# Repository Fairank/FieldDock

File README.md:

# FieldDock · Fairank / 年糕

面向 iPhone 17 Pro Max 的模块化无线与硬件实验工具。主板将 Sub-GHz、NFC、125 kHz RFID、红外、iButton、GPIO 和存储接口集中在 **94 × 40 mm** 的板上；手机承担未来的界面和结果处理。

**K 版全板布线与数字制造文件检查已完成。当前发布的是未制作、未上电的工程样板设计，尚未完成整机装配采购放行，也没有 Apple 认证或 Flipper 功能等效实测。**

## 本次交付

| 内容 | 文件 | 当前状态 |
|---|---|---|
| 可编辑电路与 PCB | [KiCad 工程](cad/FD-MAIN-01.kicad_pro)、[主板](cad/FD-MAIN-01.kicad_pcb)、[22 页原理图 PDF](schematic/FieldDock-schematic-K.pdf) | 全板布线；KiCad 10.0.6 ERC/DRC 通过 |
| 制造资料 | [Gerber / 钻孔 ZIP](manufacturing/FieldDock-PCB-K-fabrication.zip)、[加工要求](manufacturing/PROCESS-K.md)、[文件说明](manufacturing/README.md) | 已导出并独立核对几何；供应商 CAM 接单确认待完成 |
| 元件与贴装 | [BOM 复核表](manufacturing/BOM-review.csv)、[395 件贴装坐标](manufacturing/FD-MAIN-01-populated-pos.csv) | 位置已核对；部分采购料号、替代料和底面角度约定待厂家确认 |
| 结构设计 | [STEP / STL 模型包](mechanical/FieldDock-mechanical-K.zip)、[参数与生成脚本](mechanical/) | 16 个零件及组件包络；安装孔对应一致，未做实物公差验证 |
| 基础驱动 | [C 驱动与主机测试](firmware/) | CC1101 识别读取、电源预算策略、GPIO 映射；没有完整可烧录固件 |
| 可审阅证据 | [发布状态](release-status.json)、[检查记录](checks/)、[验证说明](VALIDATION.md) | 对应本次文件哈希 |

## 检查结果

- PCB DRC：**0 未连接、0 错误、0 警告**；原理图 ERC：**0 违规**。启用范围与五项默认忽略规则保留在原始报告中，不表示所有可选规则都已执行。
- 原理图、最终 PCB 和布线模型：**1,260 个已分配引脚连接一致**；57 个明确标记的未使用引脚单独核对。
- 独立 Gerber/Excellon 解析：核对 **11,385 段走线、899 个贯穿过孔、907 个金属化钻孔/槽、10 个非金属化孔**，八层铜、外形和装配坐标一致。
- 机械包络检查：50 对检查对象，无非预期交叠；4 处自攻螺钉与底孔材料交叠为设计预期。它不包含尺寸公差、插拔力和线束弯曲验证。
- 基础驱动通过主机测试与 Cortex-M4 freestanding 对象编译；尚未链接整机镜像或上板测试。

```sh
python tools/verify_artifacts.py
python tools/verify_artifacts.py --release
```

第二条命令核验本版**裸 PCB 工程样板文件**的数字检查条件，不代表供应商已接单、整机可量产或硬件功能已通过。脚本不会自动运行 KiCad。

## 硬件范围

主控为 STM32WB5MMG，射频采用 CC1101 与 ST25R3916，并设 LF RFID、红外、iButton、隔离 GPIO、microSD 及反馈控制电路。Sub-GHz、NFC 和 LF 的完整协议、读写能力与距离需要固件和样板分别验证。

两个 USB-C 分别用于手机数据/低功率输入与 AUX 固定 5 V 辅助输入，包含电源选择、限流和反向电流保护设计。**本版不含电池；两个端口的电流预算不能相加。** USB 为全速 12 Mbit/s，iPhone App 的有线数据通道尚未完成。没有增加所谓“iPhone 芯片”。

CSI、雷达、UWB、宽带 SDR、热成像和镜头检查作为外部探头方向保留；本次主板发布不等于这些探头及其算法已全部实现。Flipper 官方功能是参考目标，并未复制其固件或宣称兼容替代。仓库不包含无线网络干扰功能。

八层、1.6 mm、沉金、所有贯穿过孔树脂填孔盖帽；使用 0.30/0.15 mm 和 0.35/0.20 mm 过孔。**0.15 mm 机械钻孔是非常规加价工艺**，须按 [加工规格](manufacturing/PROCESS-K.md) 单独确认，不能按普通双层板下单。主板下单前须让厂家确认最终 CAM、叠层、填孔和阻抗条件。

## 外壳与安装

外壳目标 100 × 46 × 18 mm，安装背板另占约 1.6 mm。提供参数化源码、装配 STEP 以及各零件 STEP/STL；内部电子元件使用保守包络，并非全部来自原厂的精确三维模型。接口插拔、手机摄像头避让、固定强度、天线线圈与装壳后的射频表现仍需试装。

## 预算与后续验证

[工程预算](manufacturing/BUDGET-K.md)：单套核心样机约 **¥1,534–3,820**；两套合计约 **¥2,049–4,941**。这些是估算，**均未包含尚未报价的 0.15 mm 钻孔附加费**，也不含手机、外部探头、射频调试和返版，不是最终价格上限。没有下单或取得厂家正式报价。

下一步是供应商 CAM 与料号确认、限流上电、电源切换/倒灌测试、射频与线圈调谐、手机通信以及外壳试装。详见 [验证顺序](VALIDATION.md)。原生图纸保留设计过程的标题栏版本；本次发布以 `release-status.json` 和文件校验清单确定对应关系。

## 署名和使用

Copyright © 2026 fairank，限其依法可保护并有权许可的原创贡献。年糕图标为本项目品牌。

原创贡献以 [FieldDock 非商业许可](LICENSE) 提供源码，个人可委托收费代工制作自用样机；对许可材料的商业使用需另行获得书面许可。这是 **noncommercial source-available** 项目，不使用 OSI 开源标识。KiCad 库及其衍生部分保留上游许可，见 [第三方说明](THIRD_PARTY_NOTICES.md) 和 [逐文件来源清单](licensing/library-inventory.csv)。不主张对通用电路方法、技术事实或独立实现的排他权。

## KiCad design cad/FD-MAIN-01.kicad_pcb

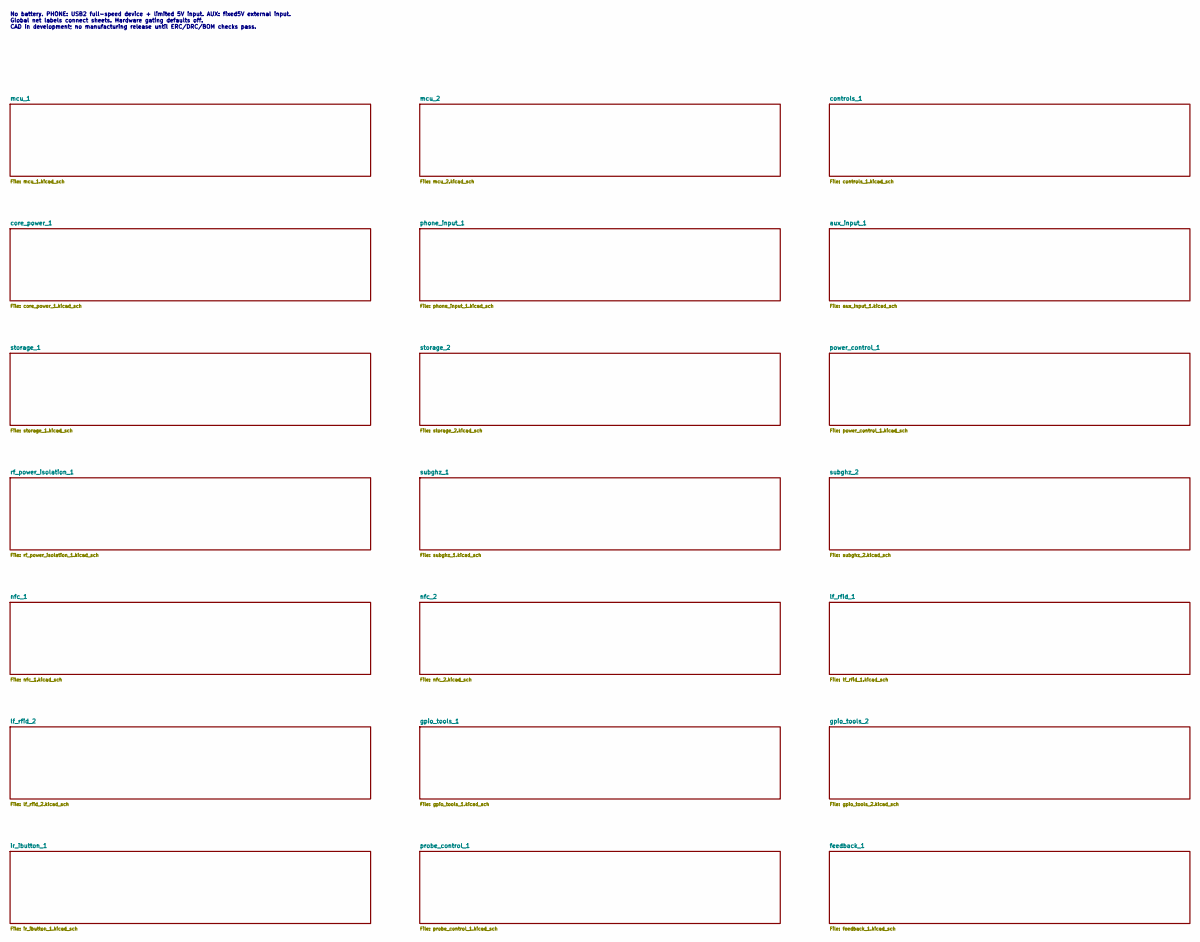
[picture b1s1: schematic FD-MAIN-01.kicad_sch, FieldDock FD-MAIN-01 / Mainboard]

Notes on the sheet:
No battery. PHONE: USB2 full-speed device + limited 5V input. AUX: fixed5V external input. Global net labels connect sheets. Hardware gating defaults off. CAD in development; no manufacturing release until ERC/DRC/BOM checks pass.

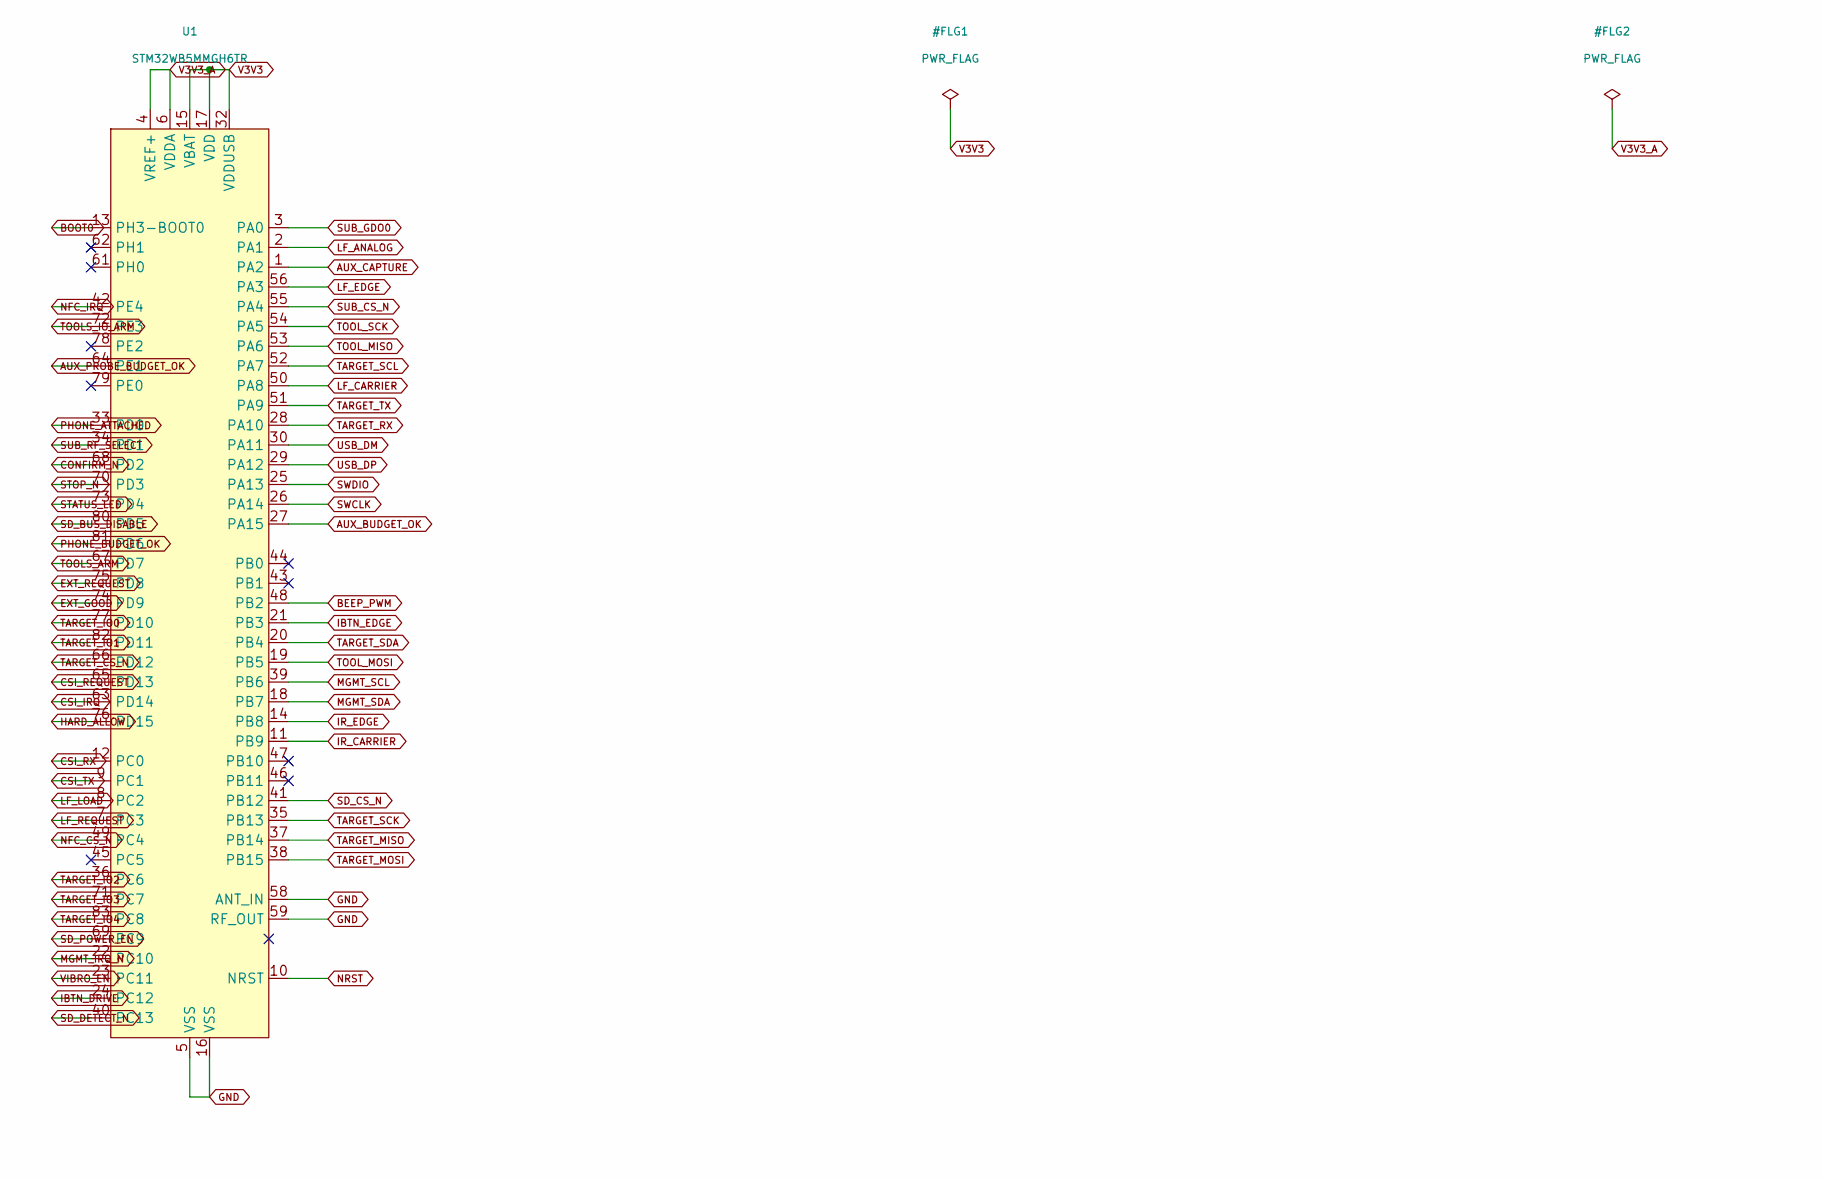
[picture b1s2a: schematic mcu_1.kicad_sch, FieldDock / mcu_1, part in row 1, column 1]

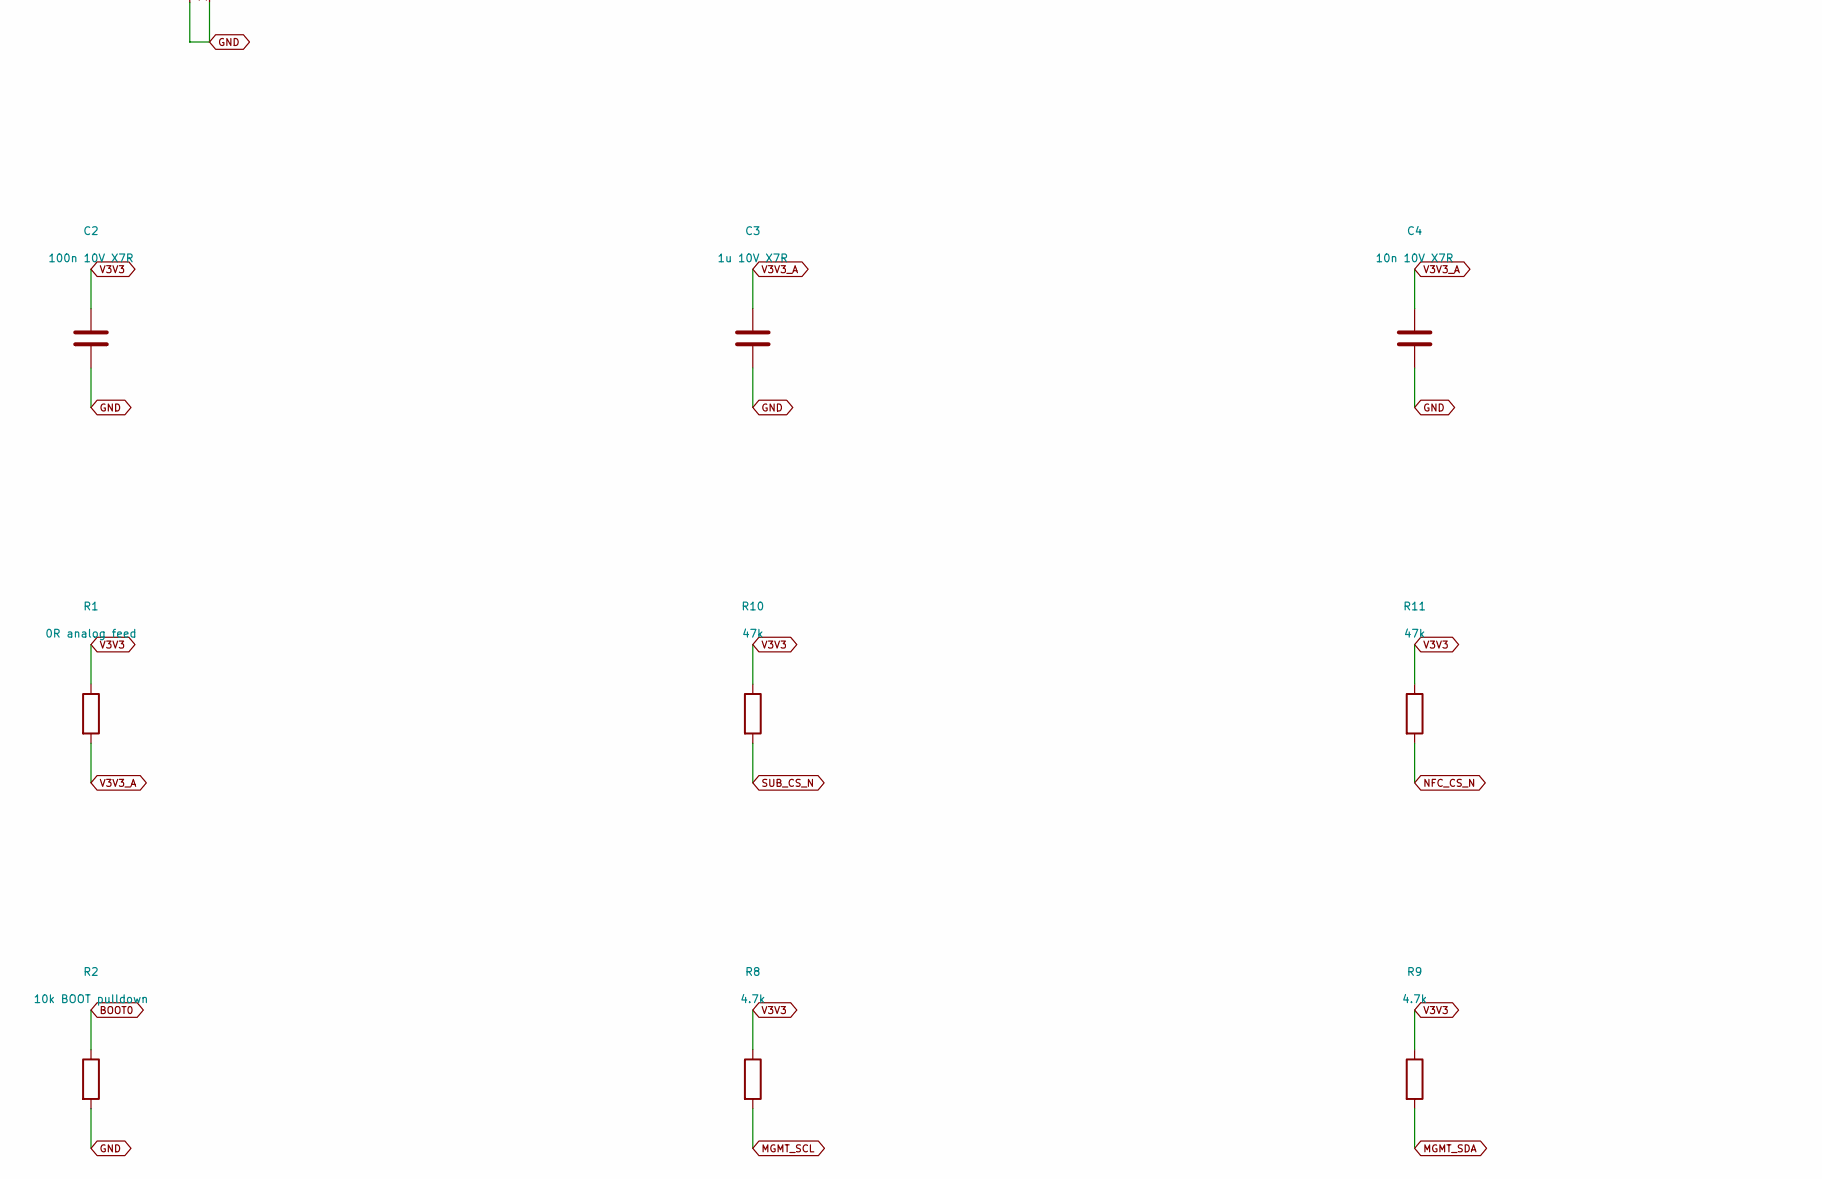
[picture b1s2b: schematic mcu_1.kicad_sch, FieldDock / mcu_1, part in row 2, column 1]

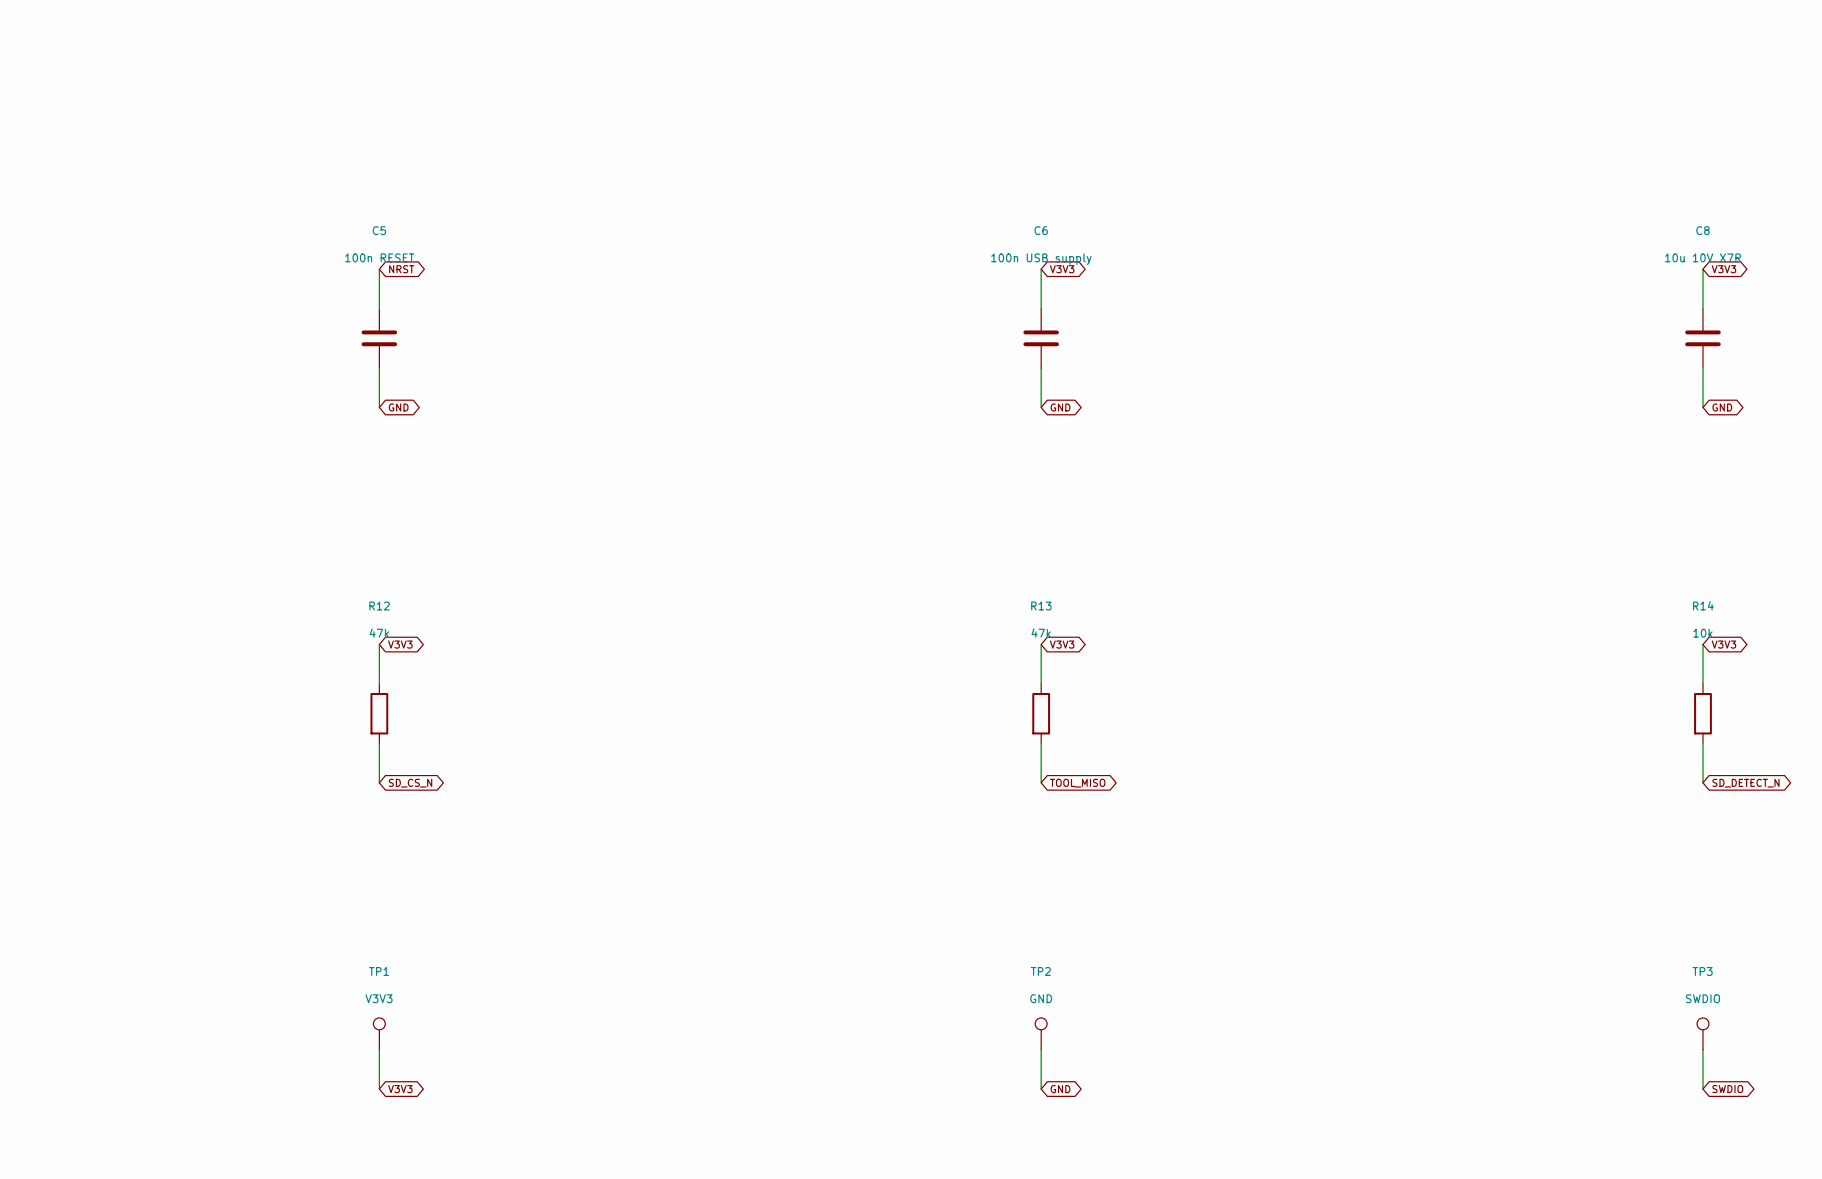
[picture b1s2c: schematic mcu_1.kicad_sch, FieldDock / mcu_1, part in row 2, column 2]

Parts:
C1: 4.7u 10V X7R; C_0805_2012Metric
C2: 100n 10V X7R; C_0603_1608Metric
C3: 1u 10V X7R; C_0603_1608Metric
C4: 10n 10V X7R; C_0603_1608Metric
C5: 100n RESET; C_0603_1608Metric
C6: 100n USB supply; C_0603_1608Metric
C8: 10u 10V X7R; C_0805_2012Metric
R1: 0R analog feed; R_0603_1608Metric
R2: 10k BOOT pulldown; R_0603_1608Metric
R8, R9: 4.7k; R_0603_1608Metric
R10, R11, R12, R13: 47k; R_0603_1608Metric
R14: 10k; R_0603_1608Metric
TP1: V3V3; TestPoint_Pad_D1.0mm
TP2: GND; TestPoint_Pad_D1.0mm
TP3: SWDIO; TestPoint_Pad_D1.0mm
U1: STM32WB5MMGH6TR; ST-SiP-LGA-86-11x7.3mm

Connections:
AUX_BUDGET_OK: U1.27 (PA15); also elsewhere on the board
AUX_CAPTURE: U1.1 (PA2); also elsewhere on the board
AUX_PROBE_BUDGET_OK: U1.64 (PE1); also elsewhere on the board
BEEP_PWM: U1.48 (PB2); also elsewhere on the board
BOOT0: R2.1, U1.13 (PH3-BOOT0); also elsewhere on the board
CONFIRM_N: U1.68 (PD2); also elsewhere on the board
CSI_IRQ: U1.63 (PD14); also elsewhere on the board
CSI_REQUEST: U1.65 (PD13); also elsewhere on the board
CSI_RX: U1.12 (PC0); also elsewhere on the board
CSI_TX: U1.9 (PC1); also elsewhere on the board
EXT_GOOD: U1.74 (PD9); also elsewhere on the board
EXT_REQUEST: U1.75 (PD8); also elsewhere on the board
GND: C1.2, C2.2, C3.2, C4.2, C5.2, C6.2, C8.2, R2.2, TP2.1, U1.5 (VSS), U1.16 (VSS), U1.31 (VSS), U1.57 (VSS), U1.58 (ANT_IN), U1.59 (RF_OUT), U1.60 (VSS), U1.84 (VSS), U1.86 (VSS); also elsewhere on the board
HARD_ALLOW: U1.76 (PD15); also elsewhere on the board
IBTN_DRIVE: U1.24 (PC12); also elsewhere on the board
IBTN_EDGE: U1.21 (PB3); also elsewhere on the board
IR_CARRIER: U1.11 (PB9); also elsewhere on the board
IR_EDGE: U1.14 (PB8); also elsewhere on the board
LF_ANALOG: U1.2 (PA1); also elsewhere on the board
LF_CARRIER: U1.50 (PA8); also elsewhere on the board
LF_EDGE: U1.56 (PA3); also elsewhere on the board
LF_LOAD: U1.8 (PC2); also elsewhere on the board
LF_REQUEST: U1.7 (PC3); also elsewhere on the board
MGMT_IRQ_N: U1.22 (PC10); also elsewhere on the board
MGMT_SCL: R8.2, U1.39 (PB6); also elsewhere on the board
MGMT_SDA: R9.2, U1.18 (PB7); also elsewhere on the board
NFC_CS_N: R11.2, U1.49 (PC4); also elsewhere on the board
NFC_IRQ: U1.42 (PE4); also elsewhere on the board
NRST: C5.1, U1.10 (NRST); also elsewhere on the board
PHONE_ATTACHED: U1.33 (PD0); also elsewhere on the board
PHONE_BUDGET_OK: U1.81 (PD6); also elsewhere on the board
SD_BUS_DISABLE: U1.80 (PD5); also elsewhere on the board
SD_CS_N: R12.2, U1.41 (PB12); also elsewhere on the board
SD_DETECT_N: R14.2, U1.40 (PC13); also elsewhere on the board
SD_POWER_EN: U1.69 (PC9); also elsewhere on the board
STATUS_LED: U1.73 (PD4); also elsewhere on the board
STOP_N: U1.70 (PD3); also elsewhere on the board
SUB_CS_N: R10.2, U1.55 (PA4); also elsewhere on the board
SUB_GDO0: U1.3 (PA0); also elsewhere on the board
SUB_RF_SELECT: U1.34 (PD1); also elsewhere on the board
SWCLK: U1.26 (PA14); also elsewhere on the board
SWDIO: TP3.1, U1.25 (PA13)
TARGET_CS_N: U1.66 (PD12); also elsewhere on the board
TARGET_IO0: U1.77 (PD10); also elsewhere on the board
TARGET_IO1: U1.82 (PD11); also elsewhere on the board
TARGET_IO2: U1.36 (PC6); also elsewhere on the board
TARGET_IO3: U1.71 (PC7); also elsewhere on the board
TARGET_IO4: U1.83 (PC8); also elsewhere on the board
TARGET_MISO: U1.37 (PB14); also elsewhere on the board
TARGET_MOSI: U1.38 (PB15); also elsewhere on the board
TARGET_RX: U1.28 (PA10); also elsewhere on the board
TARGET_SCK: U1.35 (PB13); also elsewhere on the board
TARGET_SCL: U1.52 (PA7); also elsewhere on the board
TARGET_SDA: U1.20 (PB4); also elsewhere on the board
TARGET_TX: U1.51 (PA9); also elsewhere on the board
TOOLS_ARM: U1.67 (PD7); also elsewhere on the board
TOOLS_IO_ARM: U1.72 (PE3); also elsewhere on the board
TOOL_MISO: R13.2, U1.53 (PA6); also elsewhere on the board
TOOL_MOSI: U1.19 (PB5); also elsewhere on the board
TOOL_SCK: U1.54 (PA5); also elsewhere on the board
USB_DM: U1.30 (PA11); also elsewhere on the board
USB_DP: U1.29 (PA12); also elsewhere on the board
V3V3: C1.1, C2.1, C6.1, C8.1, R1.1, R8.1, R9.1, R10.1, R11.1, R12.1, R13.1, R14.1, TP1.1, U1.15 (VBAT), U1.17 (VDD), U1.32 (VDDUSB); also elsewhere on the board
V3V3_A: C3.1, C4.1, R1.2, U1.4 (VREF+), U1.6 (VDDA)
VIBRO_EN: U1.23 (PC11); also elsewhere on the board

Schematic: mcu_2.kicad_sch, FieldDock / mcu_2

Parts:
TP4: SWCLK; TestPoint_Pad_D1.0mm
TP5: NRST; TestPoint_Pad_D1.0mm
TP6: CORE5; TestPoint_Pad_D1.0mm
TP7: EXT5; TestPoint_Pad_D1.0mm
TP8: PHONE5; TestPoint_Pad_D1.0mm

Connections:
CORE5: TP6.1; also elsewhere on the board
EXT5: TP7.1; also elsewhere on the board
NRST: TP5.1; also elsewhere on the board
PHONE5: TP8.1; also elsewhere on the board
SWCLK: TP4.1; also elsewhere on the board

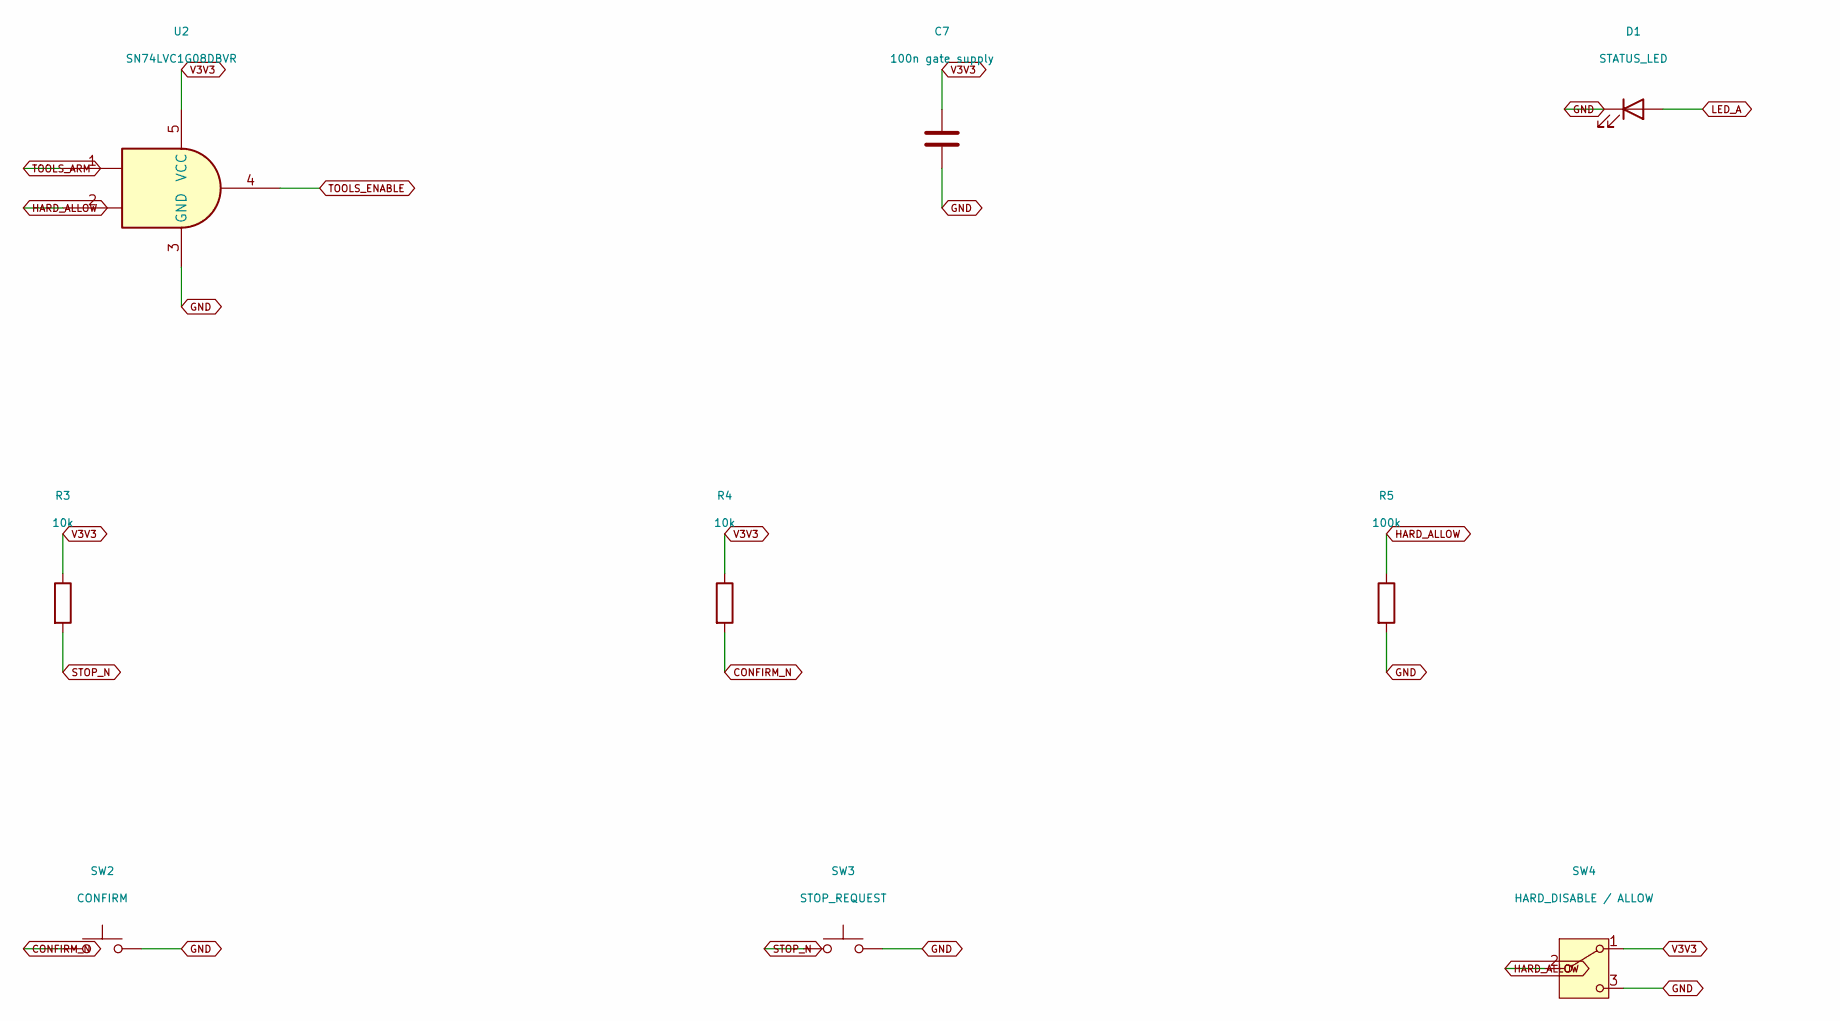
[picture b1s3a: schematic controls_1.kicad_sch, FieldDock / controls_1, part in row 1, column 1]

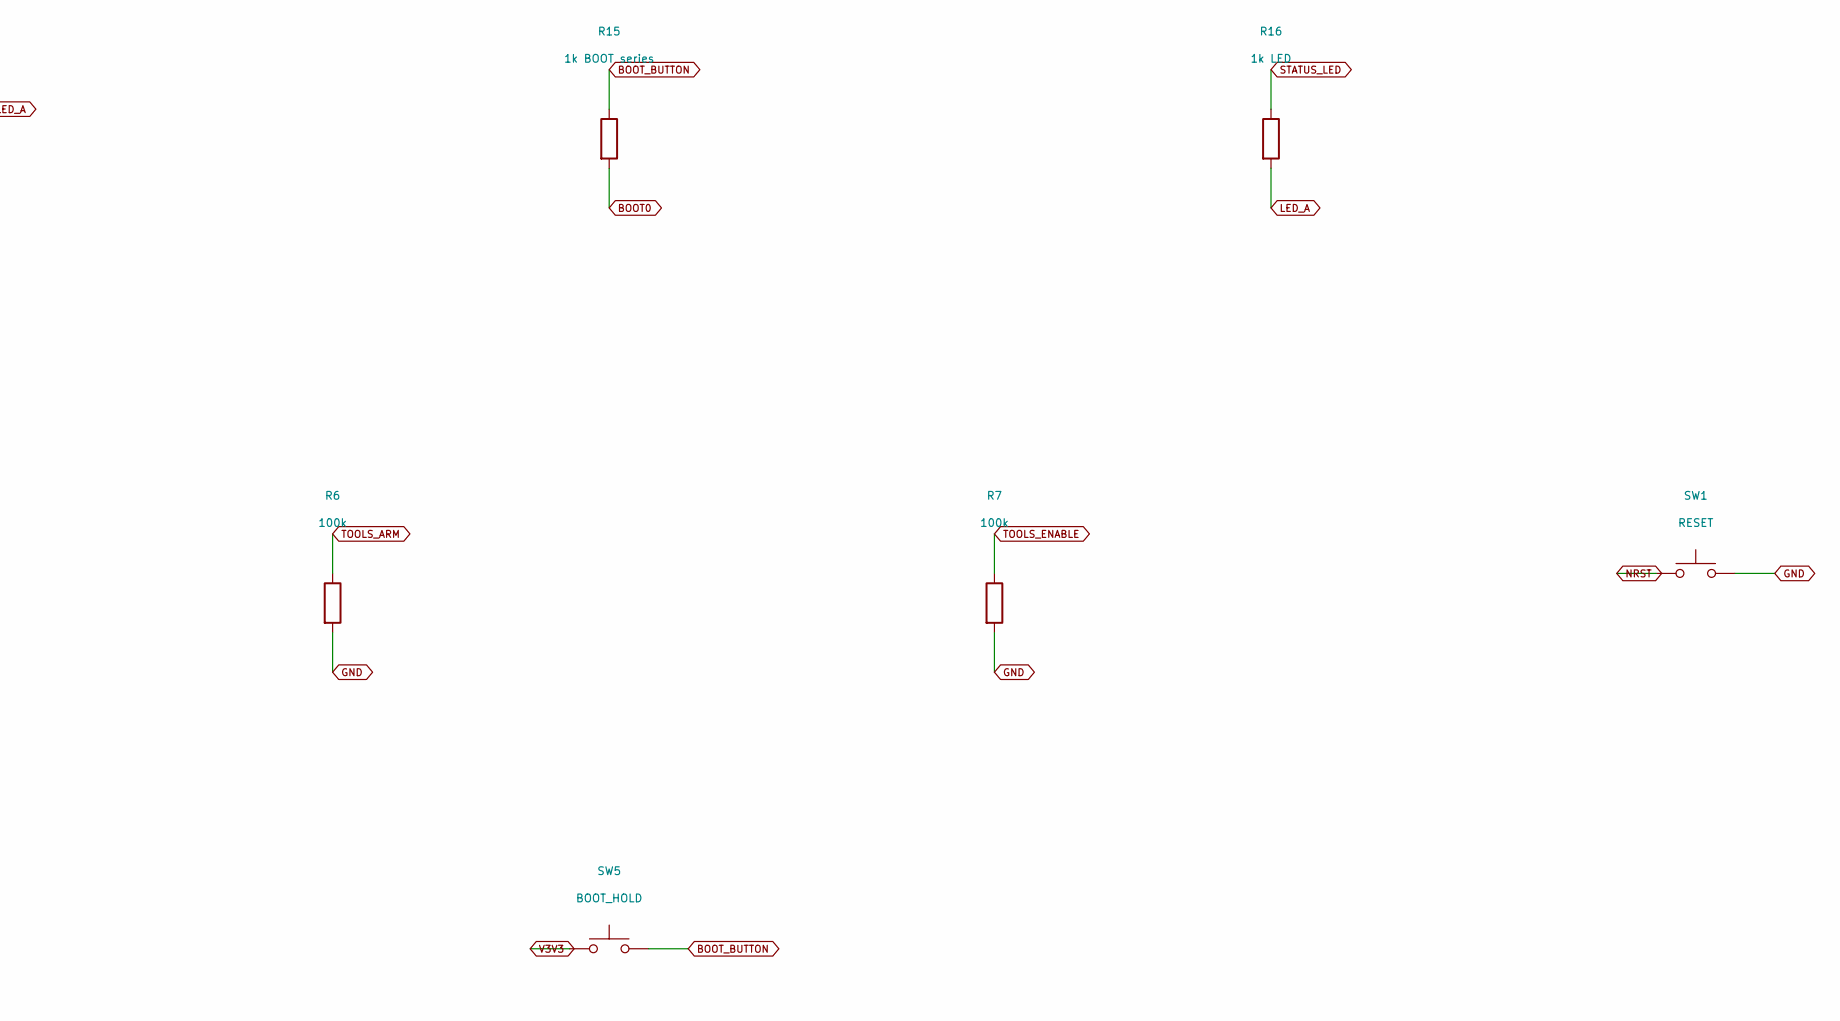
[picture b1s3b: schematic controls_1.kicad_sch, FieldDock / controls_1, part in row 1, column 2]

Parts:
C7: 100n gate supply; C_0603_1608Metric
D1: STATUS_LED; LED_0603_1608Metric
R3, R4: 10k; R_0603_1608Metric
R5, R6, R7: 100k; R_0603_1608Metric
R15: 1k BOOT series; R_0603_1608Metric
R16: 1k LED; R_0603_1608Metric
SW1: RESET; SW_SPST_TL3342
SW2: CONFIRM; SW_SPST_TL3342
SW3: STOP_REQUEST; SW_SPST_TL3342
SW4: HARD_DISABLE / ALLOW; SW_SPDT_CK_JS102011SAQN
SW5: BOOT_HOLD; SW_SPST_TL3342
U2: SN74LVC1G08DBVR; SOT-23-5

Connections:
BOOT0: R15.2; also elsewhere on the board
BOOT_BUTTON: R15.1, SW5.2
CONFIRM_N: R4.2, SW2.1; also elsewhere on the board
GND: C7.2, D1.1 (K), R5.2, R6.2, R7.2, SW1.2, SW2.2, SW3.2, SW4.3 (C), U2.3 (GND); also elsewhere on the board
HARD_ALLOW: R5.1, SW4.2 (B), U2.2; also elsewhere on the board
LED_A: D1.2 (A), R16.2
NRST: SW1.1; also elsewhere on the board
STATUS_LED: R16.1; also elsewhere on the board
STOP_N: R3.2, SW3.1; also elsewhere on the board
TOOLS_ARM: R6.1, U2.1; also elsewhere on the board
TOOLS_ENABLE: R7.1, U2.4; also elsewhere on the board
V3V3: C7.1, R3.1, R4.1, SW4.1 (A), SW5.1, U2.5 (VCC); also elsewhere on the board

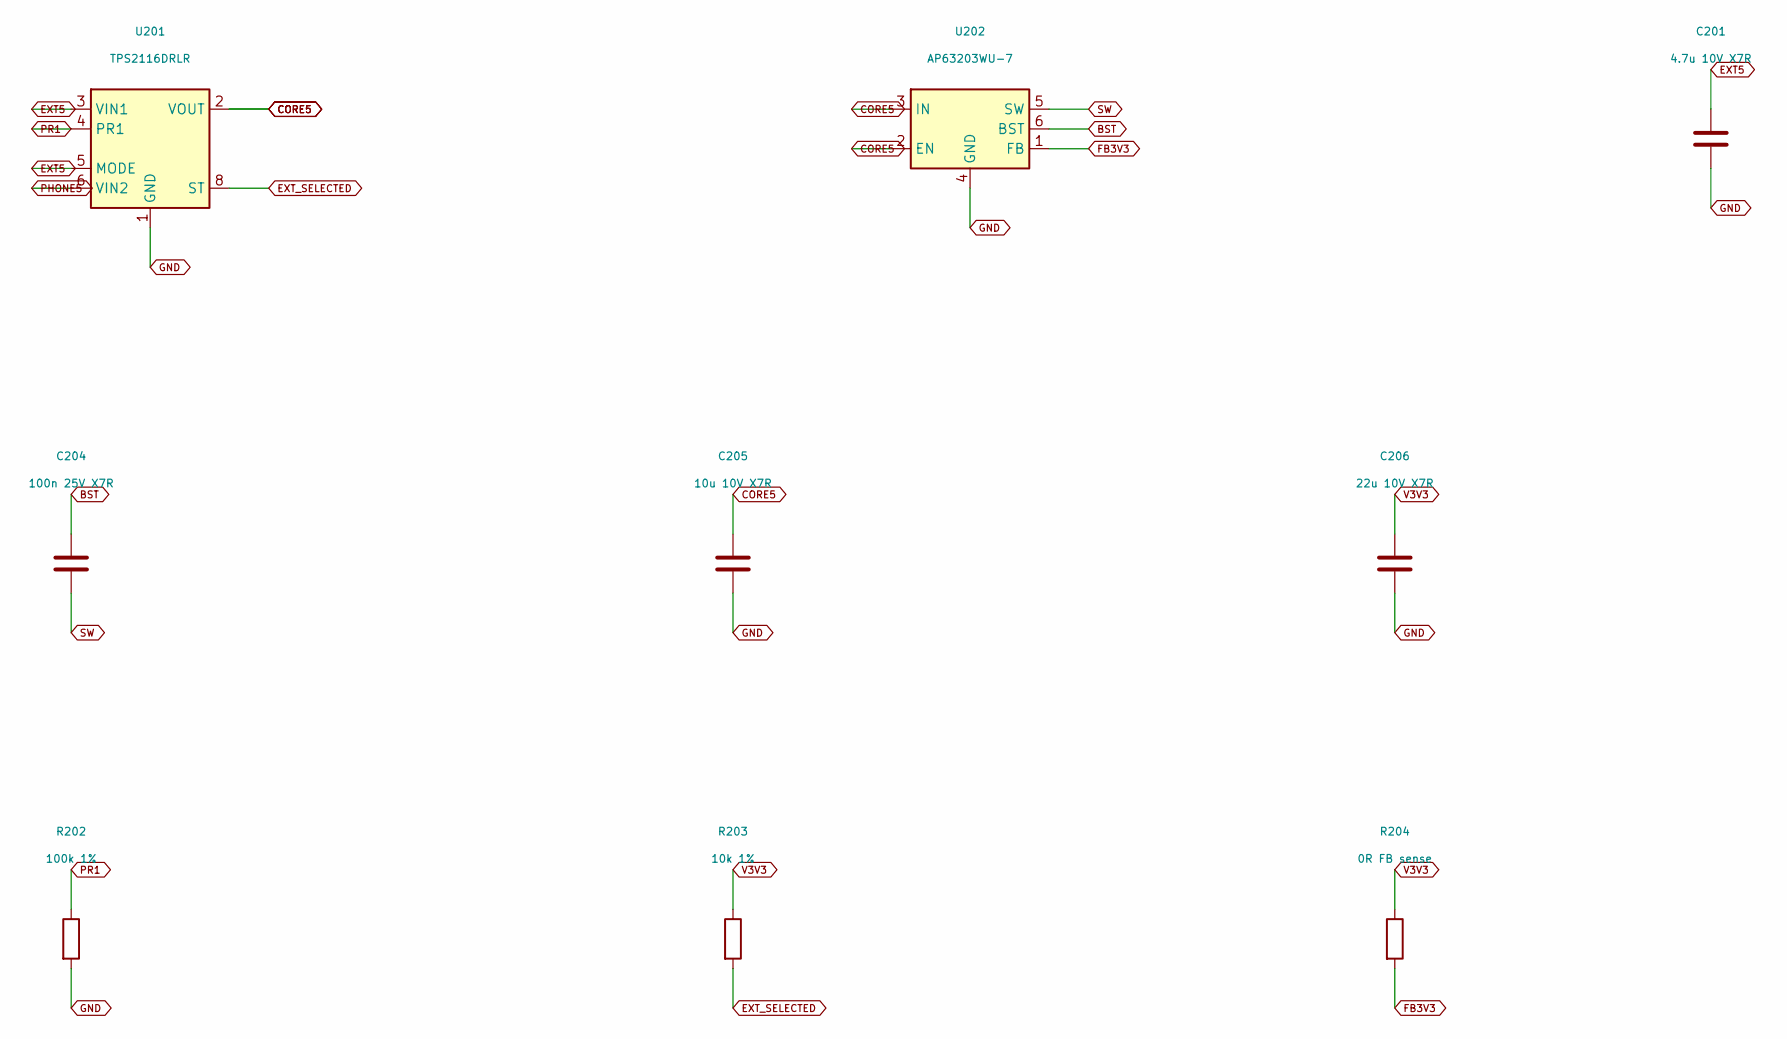
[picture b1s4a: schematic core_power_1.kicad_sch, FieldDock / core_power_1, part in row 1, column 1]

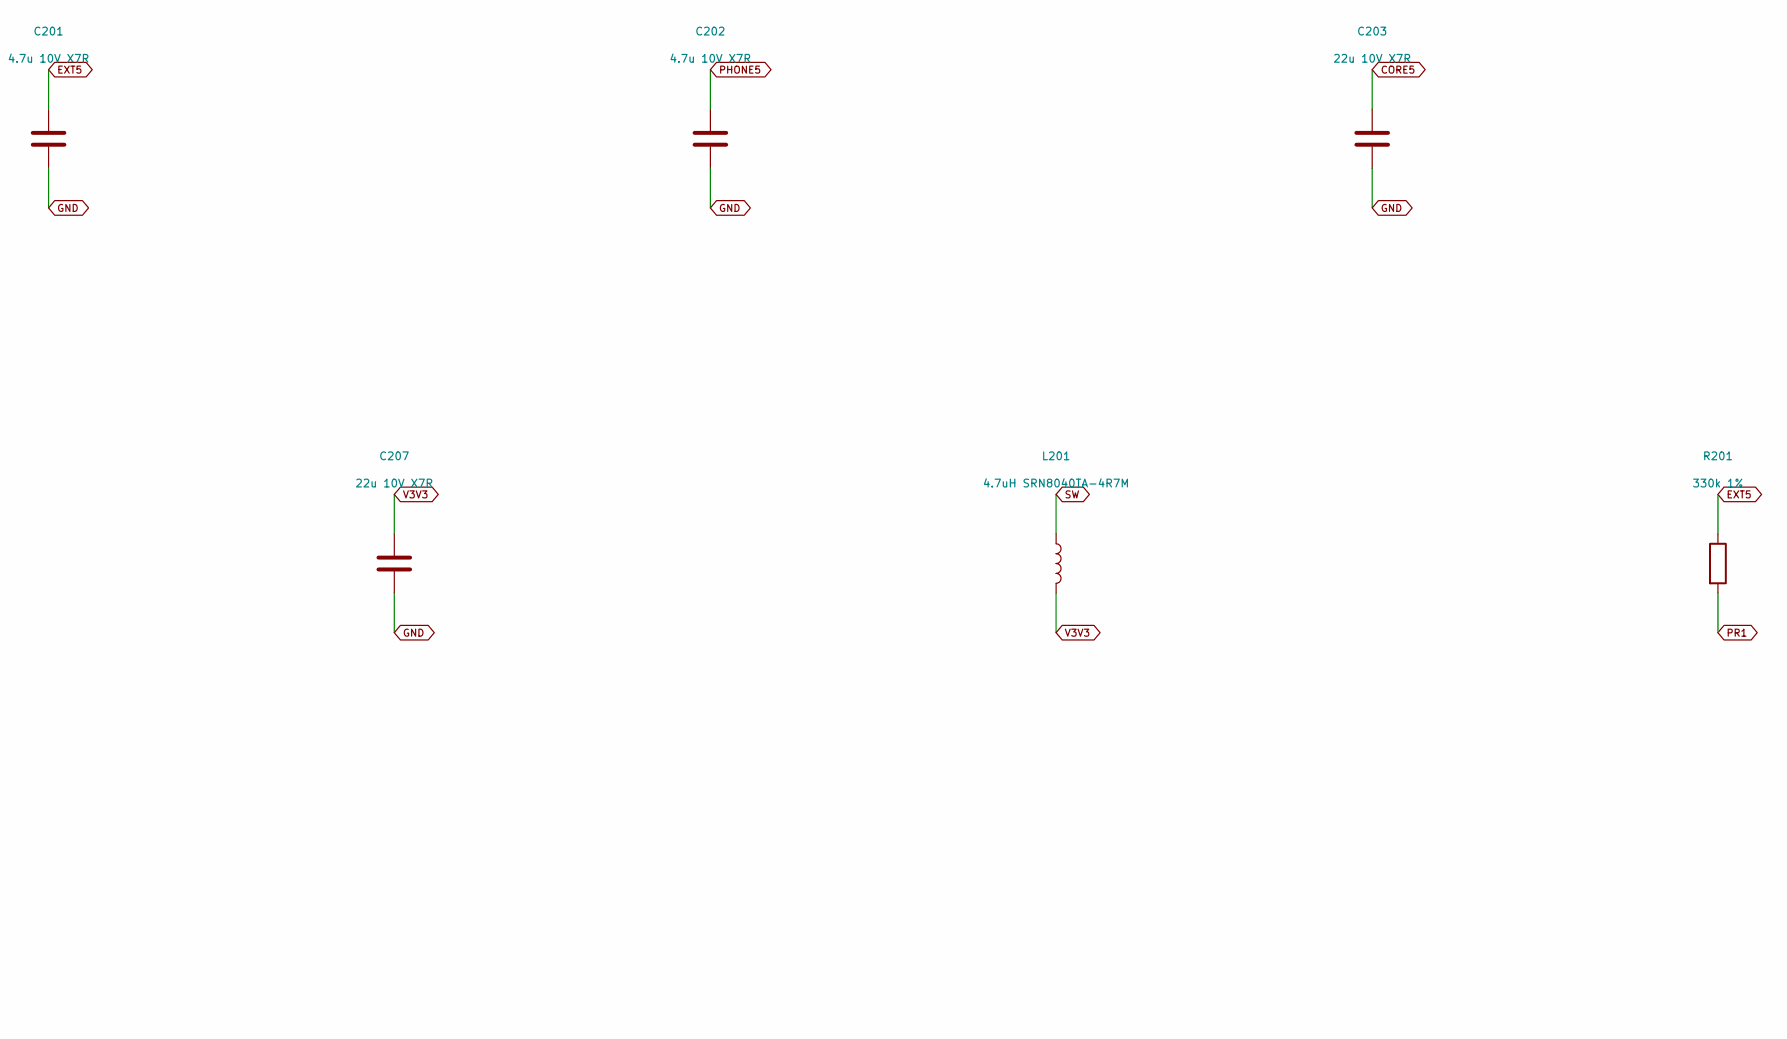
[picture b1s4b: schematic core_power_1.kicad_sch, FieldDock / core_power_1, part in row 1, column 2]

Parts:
C201, C202: 4.7u 10V X7R; C_0805_2012Metric
C203, C206, C207: 22u 10V X7R; C_1206_3216Metric
C204: 100n 25V X7R; C_0402_1005Metric
C205: 10u 10V X7R; C_0805_2012Metric
L201: 4.7uH SRN8040TA-4R7M; L_Bourns_SRN8040TA
R201: 330k 1%; R_0603_1608Metric
R202: 100k 1%; R_0603_1608Metric
R203: 10k 1%; R_0603_1608Metric
R204: 0R FB sense; R_0603_1608Metric
U201: TPS2116DRLR; SOT-583-8
U202: AP63203WU-7; TSOT-23-6

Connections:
BST: C204.1, U202.6 (BST)
CORE5: C203.1, C205.1, U201.2 (VOUT), U201.7 (VOUT), U202.2 (EN), U202.3 (IN); also elsewhere on the board
EXT5: C201.1, R201.1, U201.3 (VIN1), U201.5 (MODE); also elsewhere on the board
EXT_SELECTED: R203.2, U201.8 (ST)
FB3V3: R204.2, U202.1 (FB)
GND: C201.2, C202.2, C203.2, C205.2, C206.2, C207.2, R202.2, U201.1 (GND), U202.4 (GND); also elsewhere on the board
PHONE5: C202.1, U201.6 (VIN2); also elsewhere on the board
PR1: R201.2, R202.1, U201.4 (PR1)
SW: C204.2, L201.1, U202.5 (SW)
V3V3: C206.1, C207.1, L201.2, R203.1, R204.1; also elsewhere on the board
